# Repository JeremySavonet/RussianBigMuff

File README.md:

Russian Big Muff
====

A clone of the classic Russian Big Muff

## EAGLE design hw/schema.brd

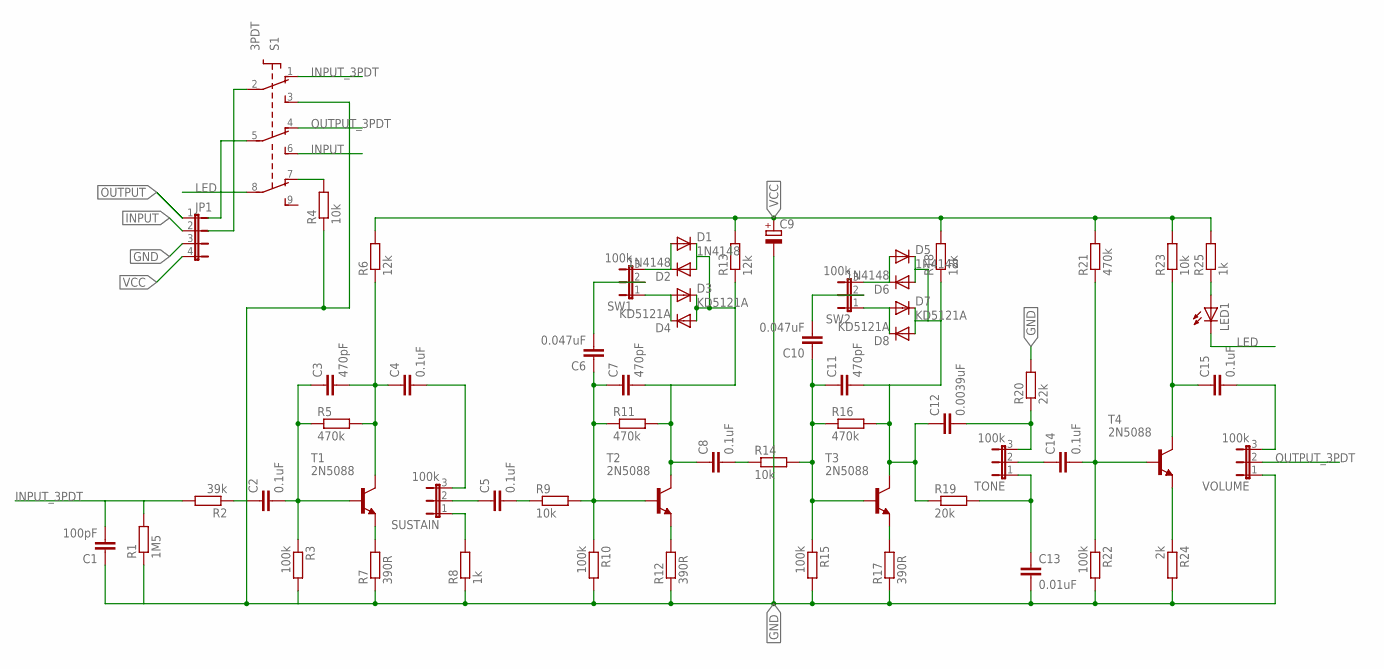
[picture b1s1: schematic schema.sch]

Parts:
C1: 100pF; C025-025X050
C2, C4, C5, C8, C14, C15: 0.1uF; C075-042X103
C3, C7, C11: 470pF; C025-025X050
C6, C10: 0.047uF; C102-043X133
C9: CPOL-EUE2.5-6; E2,5-6
C12: 0.0039uF; C050-045X075
C13: 0.01uF; C075-042X103
D1, D2, D5, D6: 1N4148; DO35-10
D3, D4, D7, D8: KD5121A; DO35-10
JP1: JP4E; JP4
LED1: LEDB155; Q62902-B155
R1: 1M5; 0204V
R2: 39k; 0204V
R3, R10, R15, R22: 100k; 0204V
R4, R9, R14, R23: 10k; 0204V
R5, R11, R16, R21: 470k; 0204V
R6, R13, R18: 12k; 0204V
R7, R12, R17: 390R; 0204V
R8, R25: 1k; 0204V
R19: 20k; 0204V
R20: 22k; 0204V
R24: 2k; 0204V
S1: 3PDT
SUSTAIN: 100k; JP2
SW1, SW2: 100k; JP2
T1, T2, T3, T4: 2N5088; TO92
TONE: 100k; JP2
VOLUME: 100k; JP2

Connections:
GND: C1.1, C9.-, C13.2, JP1.3, R1.1, R3.2, R4.1, R7.1, R8.1, R10.2, R12.1, R15.2, R17.1, R20.2, R22.2, R24.2, S1.3 (S1), VOLUME.1
INPUT: JP1.2, S1.6 (S2)
INPUT_3PDT: C1.2, R1.2, R2.2, S1.1 (O1)
LED: LED1.K (C), S1.8 (P3)
LED_3PDT: R4.2, S1.7 (O3)
unnamed: C2.2, C3.1, R3.1, R5.1, T1.2 (B)
unnamed: C2.1, R2.1
unnamed: C3.2, C4.1, R5.2, R6.1, T1.1 (C)
unnamed: R7.2, T1.3 (E)
unnamed: C6.2, SW1.2
unnamed: C14.2, R21.1, R22.1, T4.2 (B)
unnamed: C11.2, C12.1, D5.C, D6.A, D7.C, D8.A, R16.2, R18.1, R19.1, T3.1 (C)
unnamed: C4.2, SUSTAIN.3
unnamed: R8.2, SUSTAIN.1
unnamed: C5.1, SUSTAIN.2
unnamed: C15.1, R23.1, T4.1 (C)
unnamed: C5.2, R9.1
unnamed: C6.1, C7.1, R9.2, R10.1, R11.1, T2.2 (B)
unnamed: LED1.A, R25.1
unnamed: R12.2, T2.3 (E)
unnamed: R24.1, T4.3 (E)
unnamed: D7.A, D8.C, SW2.1
unnamed: C10.2, SW2.2
unnamed: C15.2, VOLUME.3
unnamed: C13.1, R19.2, TONE.1
unnamed: C12.2, R20.1, TONE.3
unnamed: C14.1, TONE.2
unnamed: D1.A, D2.C, SW1.3
unnamed: D5.A, D6.C, SW2.3
unnamed: C8.2, R14.1
unnamed: C10.1, C11.1, R14.2, R15.1, R16.1, T3.2 (B)
unnamed: C7.2, C8.1, D1.C, D2.A, D3.C, D4.A, R11.2, R13.1, T2.1 (C)
unnamed: R17.2, T3.3 (E)
OUTPUT: JP1.1
OUTPUT_3PDT: S1.4 (O2), VOLUME.2
SW1: D3.A, D4.C, SW1.1
VCC: C9.+, JP1.4, R6.2, R13.2, R18.2, R21.2, R23.2, R25.2

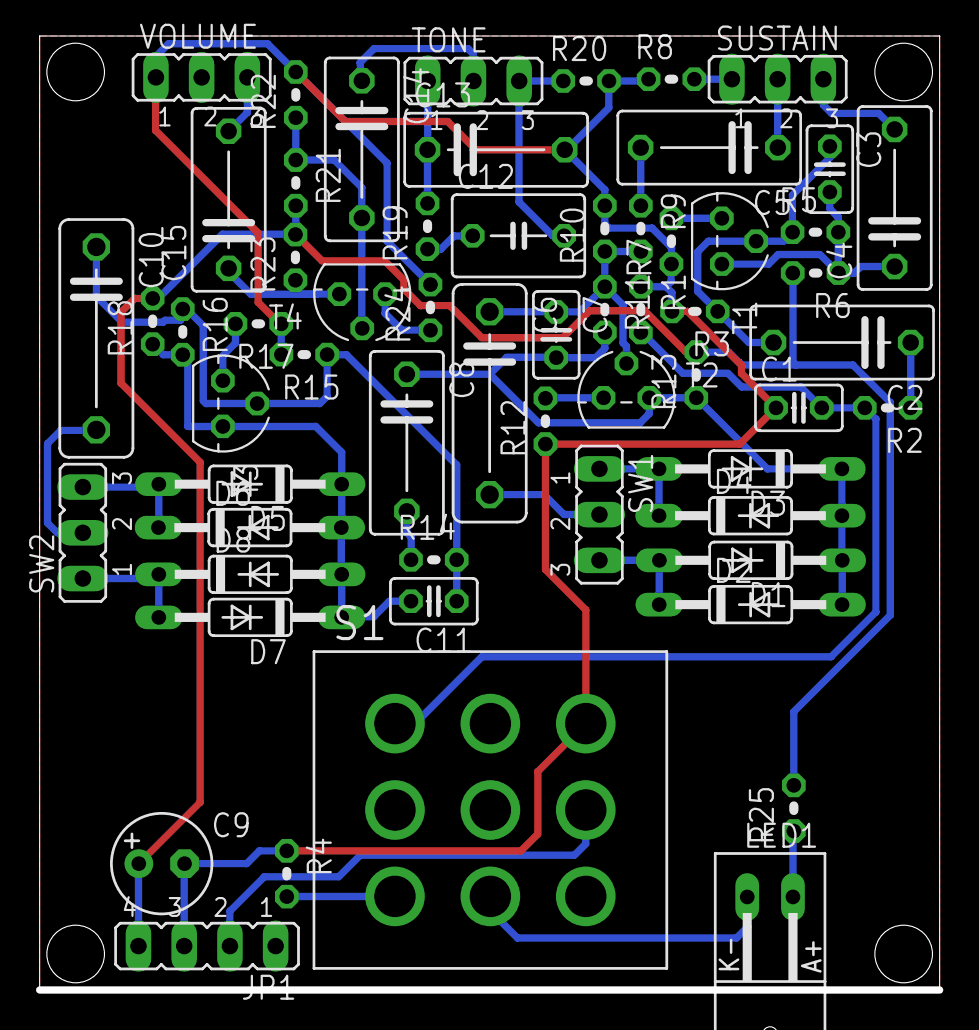
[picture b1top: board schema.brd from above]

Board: 2 copper layers, 50.0 x 53.0 mm, 60 parts (0 on the bottom side), 36 nets.

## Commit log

2018-03-06 Add schema and board: WIP
2018-03-06 Board: V2
